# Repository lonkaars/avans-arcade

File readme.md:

# Hooded Havoc: Miniboss Mania

(working title)

## hardware

- stm32 (f091rc)
- basys3 (xc7a35tcpg236-1)

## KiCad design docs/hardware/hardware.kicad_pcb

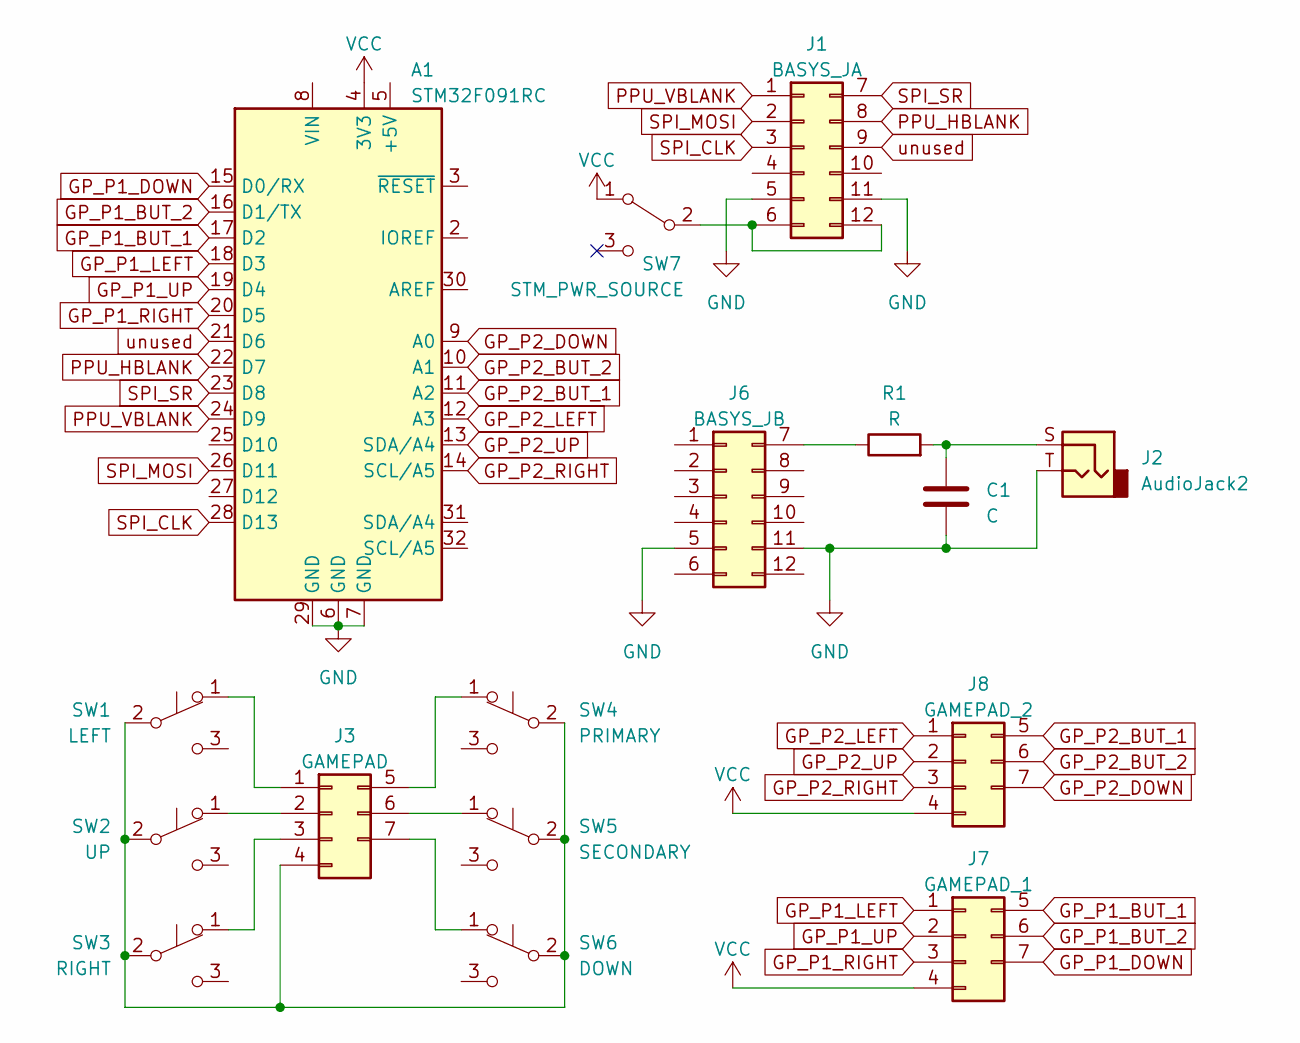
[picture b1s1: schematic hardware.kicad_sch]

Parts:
A1: STM32F091RC; Arduino_UNO_R3
C1: C; C_Disc_D6.0mm_W2.5mm_P5.00mm
J1: BASYS_JA; PinHeader_2x06_P2.54mm_Vertical
J2: AudioJack2; Jack_3.5mm_CUI_SJ1-3523N_Horizontal
J3: GAMEPAD; PinHeader_2x04_P2.54mm_Vertical
J6: BASYS_JB; PinHeader_2x06_P2.54mm_Vertical
J7: GAMEPAD_1; PinHeader_2x04_P2.54mm_Vertical
J8: GAMEPAD_2; PinHeader_2x04_P2.54mm_Vertical
R1: R; R_Axial_DIN0207_L6.3mm_D2.5mm_P7.62mm_Horizontal
SW1: LEFT; SW_PUSH_6mm
SW2: UP; SW_PUSH_6mm
SW3: RIGHT; SW_PUSH_6mm
SW4: PRIMARY; SW_PUSH_6mm
SW5: SECONDARY; SW_PUSH_6mm
SW6: DOWN; SW_PUSH_6mm
SW7: STM_PWR_SOURCE; SW_Slide_1P2T_CK_OS102011MS2Q

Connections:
GND: A1.6 (GND), A1.7 (GND), A1.29 (GND), C1.2, J1.5, J1.11, J2.T, J6.5, J6.11
GP_P1_BUT_1: A1.17 (D2), J7.5 (RIGHT)
GP_P1_BUT_2: A1.16 (D1/TX), J7.6 (PRIMARY)
GP_P1_DOWN: A1.15 (D0/RX), J7.7 (SECONDARY)
GP_P1_LEFT: A1.18 (D3), J7.1 (UP)
GP_P1_RIGHT: A1.20 (D5), J7.3 (LEFT)
GP_P1_UP: A1.19 (D4), J7.2 (DOWN)
GP_P2_BUT_1: A1.11 (A2), J8.5 (RIGHT)
GP_P2_BUT_2: A1.10 (A1), J8.6 (PRIMARY)
GP_P2_DOWN: A1.9 (A0), J8.7 (SECONDARY)
GP_P2_LEFT: A1.12 (A3), J8.1 (UP)
GP_P2_RIGHT: A1.14 (SCL/A5), J8.3 (LEFT)
GP_P2_UP: A1.13 (SDA/A4), J8.2 (DOWN)
unnamed: C1.1, J2.S, R1.2
unnamed: J1.6, J1.12, SW7.2 (B)
unnamed: J3.2 (DOWN), SW2.1 (A)
unnamed: J3.3 (LEFT), SW3.1 (A)
unnamed: J3.6 (PRIMARY), SW5.1 (A)
unnamed: J3.5 (RIGHT), SW4.1 (A)
unnamed: J3.7 (SECONDARY), SW6.1 (A)
unnamed: J3.1 (UP), SW1.1 (A)
unnamed: J3.4 (VCC), SW1.2 (B), SW2.2 (B), SW3.2 (B), SW4.2 (B), SW5.2 (B), SW6.2 (B)
unnamed: J6.7, R1.1
PPU_HBLANK: A1.22 (D7), J1.8
PPU_VBLANK: A1.24 (D9), J1.1
SPI_CLK: A1.28 (D13), J1.3
SPI_MOSI: A1.26 (D11), J1.2
SPI_SR: A1.23 (D8), J1.7
VCC: A1.4 (3V3), J7.4 (VCC), J8.4 (VCC), SW7.1 (A)
unused: A1.21 (D6), J1.9

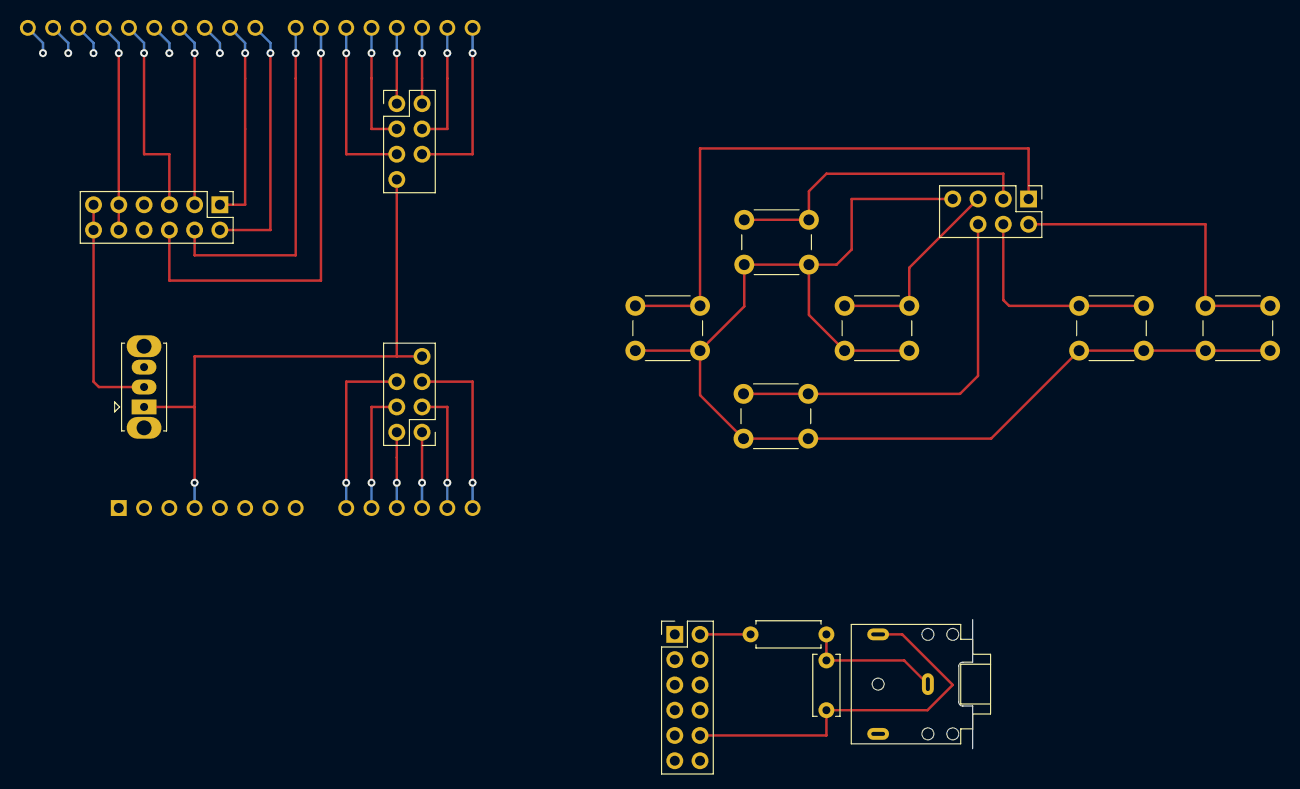
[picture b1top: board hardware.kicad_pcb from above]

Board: 2 copper layers, 16 parts (1 on the bottom side), 30 nets.

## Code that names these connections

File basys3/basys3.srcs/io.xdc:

set_property IOSTANDARD LVCMOS33 [get_ports SPI_MOSI]
set_property PACKAGE_PIN L2 [get_ports SPI_MOSI]

set_property PACKAGE_PIN J2 [get_ports SPI_CLK]
set_property IOSTANDARD LVCMOS33 [get_ports SPI_CLK]

set_property IOSTANDARD LVCMOS33 [get_ports SPI_SR]
set_property PACKAGE_PIN H1 [get_ports SPI_SR]
set_property PULLDOWN true [get_ports SPI_SR]



set_property IOSTANDARD LVCMOS33 [get_ports HBLANK]
set_property PACKAGE_PIN K2 [get_ports HBLANK]

set_property IOSTANDARD LVCMOS33 [get_ports VBLANK]
set_property PACKAGE_PIN J1 [get_ports VBLANK]



set_property IOSTANDARD LVCMOS33 [get_ports SYSCLK]
set_property PACKAGE_PIN W5 [get_ports SYSCLK]

set_property IOSTANDARD LVCMOS33 [get_ports RESET]
set_property PACKAGE_PIN T18 [get_ports RESET]

set_property IOSTANDARD LVCMOS33 [get_ports HSYNC]
set_property IOSTANDARD LVCMOS33 [get_ports VSYNC]

set_property PACKAGE_PIN P19 [get_ports HSYNC]
set_property PACKAGE_PIN R19 [get_ports VSYNC]

set_property IOSTANDARD LVCMOS33 [get_ports {R[3]}]
set_property IOSTANDARD LVCMOS33 [get_ports {R[2]}]
set_property IOSTANDARD LVCMOS33 [get_ports {R[1]}]
set_property IOSTANDARD LVCMOS33 [get_ports {R[0]}]
set_property IOSTANDARD LVCMOS33 [get_ports {G[3]}]
set_property IOSTANDARD LVCMOS33 [get_ports {G[2]}]
set_property IOSTANDARD LVCMOS33 [get_ports {G[1]}]
set_property IOSTANDARD LVCMOS33 [get_ports {G[0]}]
set_property IOSTANDARD LVCMOS33 [get_ports {B[3]}]
set_property IOSTANDARD LVCMOS33 [get_ports {B[2]}]
set_property IOSTANDARD LVCMOS33 [get_ports {B[1]}]
set_property IOSTANDARD LVCMOS33 [get_ports {B[0]}]

set_property PACKAGE_PIN N19 [get_ports {R[3]}]
set_property PACKAGE_PIN J19 [get_ports {R[2]}]
set_property PACKAGE_PIN H19 [get_ports {R[1]}]
set_property PACKAGE_PIN G19 [get_ports {R[0]}]
set_property PACKAGE_PIN D17 [get_ports {G[3]}]
set_property PACKAGE_PIN G17 [get_ports {G[2]}]
set_property PACKAGE_PIN H17 [get_ports {G[1]}]
set_property PACKAGE_PIN J17 [get_ports {G[0]}]
set_property PACKAGE_PIN J18 [get_ports {B[3]}]
set_property PACKAGE_PIN K18 [get_ports {B[2]}]
set_property PACKAGE_PIN L18 [get_ports {B[1]}]
set_property PACKAGE_PIN N18 [get_ports {B[0]}]

set_property IOSTANDARD LVCMOS33 [get_ports DBG_DISP_ADDR]
set_property PACKAGE_PIN R2 [get_ports DBG_DISP_ADDR]
set_property IOSTANDARD LVCMOS33 [get_ports {DBG_LEDS_OUT[15]}]
set_property IOSTANDARD LVCMOS33 [get_ports {DBG_LEDS_OUT[14]}]
set_property IOSTANDARD LVCMOS33 [get_ports {DBG_LEDS_OUT[13]}]
set_property IOSTANDARD LVCMOS33 [get_ports {DBG_LEDS_OUT[12]}]
set_property IOSTANDARD LVCMOS33 [get_ports {DBG_LEDS_OUT[11]}]
set_property IOSTANDARD LVCMOS33 [get_ports {DBG_LEDS_OUT[10]}]
set_property IOSTANDARD LVCMOS33 [get_ports {DBG_LEDS_OUT[8]}]
set_property IOSTANDARD LVCMOS33 [get_ports {DBG_LEDS_OUT[9]}]
set_property IOSTANDARD LVCMOS33 [get_ports {DBG_LEDS_OUT[7]}]
set_property IOSTANDARD LVCMOS33 [get_ports {DBG_LEDS_OUT[6]}]
set_property IOSTANDARD LVCMOS33 [get_ports {DBG_LEDS_OUT[5]}]
set_property IOSTANDARD LVCMOS33 [get_ports {DBG_LEDS_OUT[4]}]
set_property IOSTANDARD LVCMOS33 [get_ports {DBG_LEDS_OUT[3]}]
set_property IOSTANDARD LVCMOS33 [get_ports {DBG_LEDS_OUT[2]}]
set_property IOSTANDARD LVCMOS33 [get_ports {DBG_LEDS_OUT[1]}]
set_property IOSTANDARD LVCMOS33 [get_ports {DBG_LEDS_OUT[0]}]
set_property PACKAGE_PIN L1 [get_ports {DBG_LEDS_OUT[15]}]
set_property PACKAGE_PIN P1 [get_ports {DBG_LEDS_OUT[14]}]
set_property PACKAGE_PIN N3 [get_ports {DBG_LEDS_OUT[13]}]
set_property PACKAGE_PIN P3 [get_ports {DBG_LEDS_OUT[12]}]
set_property PACKAGE_PIN U3 [get_ports {DBG_LEDS_OUT[11]}]
set_property PACKAGE_PIN W3 [get_ports {DBG_LEDS_OUT[10]}]
set_property PACKAGE_PIN V3 [get_ports {DBG_LEDS_OUT[9]}]
set_property PACKAGE_PIN V13 [get_ports {DBG_LEDS_OUT[8]}]
set_property PACKAGE_PIN V14 [get_ports {DBG_LEDS_OUT[7]}]
set_property PACKAGE_PIN U14 [get_ports {DBG_LEDS_OUT[6]}]
set_property PACKAGE_PIN U15 [get_ports {DBG_LEDS_OUT[5]}]
set_property PACKAGE_PIN W18 [get_ports {DBG_LEDS_OUT[4]}]
set_property PACKAGE_PIN V19 [get_ports {DBG_LEDS_OUT[3]}]
set_property PACKAGE_PIN U19 [get_ports {DBG_LEDS_OUT[2]}]
set_property PACKAGE_PIN E19 [get_ports {DBG_LEDS_OUT[1]}]
set_property PACKAGE_PIN U16 [get_ports {DBG_LEDS_OUT[0]}]


set_property CONFIG_VOLTAGE 3.3 [current_design]
set_property CFGBVS VCCO [current_design]

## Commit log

2023-02-02 added sound chips research
2023-02-03 rename sound chip research to research.md
2023-02-03 beginning of gpu research added
2023-02-03 add makefile for bin tests
2023-02-05 add more PPU design
2023-02-06 add spreadsheet link to research.md
2023-02-07 more PPU documentation
2023-02-08 more PPU design
2023-02-08 more PPU (level 3 design)
2023-02-09 add style guide + formatters
2023-02-10 PPU resolution change
2023-02-11 added gameplay concept
2023-02-12 Create Research game engine
2023-02-13 Research - FPGA audio generation
2023-02-13 player sprite concept
2023-02-13 Create Game Idea Bjorn
2023-02-13 Mijn toevegingen
2023-02-13 test
2023-02-13 Added Bjorn concept
2023-02-13 elaborate gameplay concept
2023-02-14 add student ids to document template
2023-02-14 fix line wrapping in gameplay.md
2023-02-14 move architecture from research into architecture.md and update ppu design files
2023-02-14 architecture top-level added
2023-02-15 GameEngine
2023-02-15 Quick spelling check
2023-02-15 APU Archetecture.md
2023-02-15 Update architecture.md
    Updated controller design
2023-02-15 fix markdown for document converter
2023-02-15 architecture
2023-02-15 APU tone generation
2023-02-15 final architecture document version
2023-02-17 fix project name in document template
2023-02-17 WIP ppu.vhdl
2023-02-17 safety commit (before remove DI lines)
2023-02-17 separate AUX memory into separate component
2023-02-17 use tabs for indentation
2023-02-18 ppu pceg done + ppu top.vhdl done
2023-02-18 no clock output while reset high in pceg
2023-02-19 apu note 2 freq
2023-02-19 single frequency implementation
2023-02-19 apu_LUT_reader made with variable frequency
2023-02-19 add list of abbreviations to docs folder
2023-02-19 separate constants file for vhdl code
2023-02-19 finish ppu address decoder
2023-02-19 format and add apu sources to vivado project file
2023-02-19 polish on APU_N2F
2023-02-19 hello world over usb serial done
2023-02-19 shifted triangle wave 180*
2023-02-19 small formatting fix
2023-02-19 POC done
2023-02-20 rename .vhdl to .vhd
2023-02-20 exposed ram module implemented
2023-02-20 update code style
2023-02-20 PPU AUX memory finished and tested
2023-02-20 update TMM data width + update memory map (WIP ppu_sprite_bg)
2023-02-20 PPU background sprite component done (but unverified)
2023-02-21 fix sprite flip axes swapped
2023-02-21 PPU debugged and working (but with unwanted latches)
2023-02-21 background sprite component done, tested, and working without latches
2023-02-21 WIP ppu foreground sprite component
2023-02-21 WIP foreground sprite + `std_logic_vector` -> `unsigned` mess
2023-02-22 WIP ppu fg sprite fetch logic
2023-02-23 ppu foreground sprite working and ~50% tested
2023-02-23 plut,comp en vga
2023-02-23 sdl2 demo
2023-02-23 clock
    interne clcok toegevoegd aan de vga modules. niks is veranderd aan de PLUT want die werkt nog steeds op dezelfde SYSCLK.
2023-02-23 aanpassingen
    was counter naar 0 vergeten
2023-02-24 WIP ppu interface
2023-02-24 update style guide and format code
2023-02-24 rename and move files
2023-02-24 desktop compilation options in makefile
2023-02-24 mv sdl2 demo to src/ppusim folder
2023-02-24 ppusim refactor
2023-02-24 c interface semi-done
2023-02-24 WIP ppusim
2023-02-24 background sprites working in ppusim
2023-02-25 ppusim done
2023-02-25 optimize ppusim with threads
2023-02-25 update/fix build config for windows
2023-02-25 limit thread count to core count
2023-02-25 add developer documentation to ppusim/ppu interface
2023-02-25 fix src readme
2023-02-25 fix compiler warnings from `hh_ppu_vram_valid_address`
2023-03-01 WIP addr_dec timing check + ppu address bus fix
2023-03-02 ExampleCode For physics
2023-03-03 apu constants cleanup
2023-03-03 file cleanup
2023-03-03 fix apu_note_to_frequency
2023-03-03 WIP fg sprite optimilization
2023-03-03 State digrams for gameLogic
2023-03-03 fix naming style
2023-03-03 New Folder for stm32 gamelogic
2023-03-03 Player movement x/y with collision map
    Player can move in x and y direction via 4 buttons
    Furthermore there is a tilemap included for collisions for coresponding map design
2023-03-03 changed to .md and added pin layout
2023-03-03 Changed to tables
2023-03-03 Cleaned main.c
2023-03-04 foreground sprite optimization (untested) done
2023-03-04 fix multiple driver net errors
2023-03-07 some func defenitions for game-engine and foundation
2023-03-08 more todo's
2023-03-08 fix windows build system and add vscode configuration files
2023-03-08 scaffold vga display controller and upscaler
2023-03-08 spelling correction
2023-03-08 WIP dispctl
2023-03-08 more WIP dispctl
2023-03-08 ppu dispctl WIP (shift XY output 2 scanlines and send THVBLANK)
2023-03-08 ppu_dispctl test for valid VGA signal using DMT 640x480 @ 60
2023-03-09 Add files via upload
    Updated with functions
2023-03-10 code
2023-03-10 added define for fixed point maths
2023-03-10 nope
2023-03-10 initial merge of #26
2023-03-10 add input emulation to test collision
2023-03-10 `clang-format`
2023-03-10 update style guide
2023-03-10 fixed code styles
2023-03-10 move pinout.md to schematic
2023-03-10 top.vhdl
2023-03-10 ppusim read sprites from file and put into vram
2023-03-10 removed TODO
2023-03-11 moved files
2023-03-11 Camera function V1
2023-03-11 makefile engine
2023-03-11 Camera.c and Camera.h
2023-03-11 add display diagram for ppu
2023-03-11 drawing map en read from binary complete. shift to background.
2023-03-11 Fixed movement
    Adjusted movement speed otherwise wouldnt show any movement. Also changed input testing lines so it does work
2023-03-12 integrated palettes and fixed reading tiles
2023-03-12 syntax update
2023-03-12 camera movement
2023-03-12 makefile update
2023-03-12 WIP dispctl (valid VGA signal)
2023-03-12 upscaler test with coe initialized rom
2023-03-13 features voor ons spel
2023-03-13 camera, movement, collisions
2023-03-13 demo.c
2023-03-13 camera.c en camera.h
2023-03-13 Background collision
    Added background collision for player and other entities. Added gravity and jump functionailty
2023-03-13 demo.c clean up
2023-03-13 Revert "Merge branch 'dev' of https://github.com/Flenk008/avans-arcade into dev"
    This reverts commit 4f489426e05fb3b296998b17859d8702cc4f37e1, reversing
    changes made to e47f7fa198229b8598b8ab03ef8b2483f7c685bc.
2023-03-13 Revert "Background collision"
    This reverts commit e47f7fa198229b8598b8ab03ef8b2483f7c685bc.
2023-03-13 Revert "Revert "Merge branch 'dev' of https://github.com/Flenk008/avans-arcade into dev""
    This reverts commit a9ad8e0a8ac5346108f1e2c1a0bf9360fadc20da.
2023-03-13 fix display upscaler (output working!)
2023-03-13 working bitstream generation
2023-03-13 untested POC
2023-03-13 fix write enable input line
2023-03-14 camera y-axis bug fixed + clean up
2023-03-14 update hardware schematics for ppu testing
2023-03-14 added hexdump file structures
2023-03-14 WIP ppu testing
2023-03-14 finalize hardware
2023-03-14 add fp-info-cache to gitignore
2023-03-15 precautions
2023-03-15 game loop and bullet
    TODO game loop:
    -(startingscreen) read correct indexes
    -(shop) read correct indexes
    -gameplay still needs alot with different levels etc..
    rest not yet done
    bullet needs testing and correct PAL and tilemap reading
2023-03-15 architecture docu
2023-03-15 Player-Enemy collision
    Added player with enemy collision. Also changed input system to a vector system with friction and gravity. Jump also works. Enemy is 1 stationary object.
2023-03-15 architecture and design
2023-03-15 added title screen
2023-03-15 Update features.md
    Added Dubble Jump
2023-03-15 updated file fetch
2023-03-15 (UNCLEAN) partial merge of #37
2023-03-15 architecture document update
2023-03-16 Added top level stm
2023-03-16 Update architecture.md
    Added SPI (STM32, BASYS3)
2023-03-16 restructure architecture document
2023-03-20 debugged the ppu (still WIP, but some output is visible)
2023-03-20 faster SPI clock
2023-03-20 demo version
2023-03-22 merge
2023-03-22 tilemap build system done
2023-03-22 add static makefile targets to main gamefile, and add target to flash static rom to stm32
2023-03-22 fix endianness in `tilepack` and add `tilemap2png` script for previewing finished tilemap
2023-03-22 Animated jumpable slime
2023-03-22 updated test/bin/.gitignore
2023-03-22 added normal slime animations
2023-03-22 load static/tilemap.bin in ppusim
2023-03-23 use sort order in makefile and add air tile at index 0
2023-03-23 added font.hex
2023-03-23 fixed slime.hex
2023-03-23 add scripts for converting tiles to separate png images for tilemap editing
2023-03-23 WIP testing ppu (fixed BAM 2nat buffer overflow)
2023-03-24 add power source toggle switch to hardware schematics
2023-03-24 added first pass on animation systems
2023-03-24 a little clean up of player_controller.c
2023-03-29 update pipeline
2023-03-29 more debugging WIP
2023-03-30 gameloop/bullet/levels
    gameloop moet nog wat gefixt worden. shop moet nog wat art en functie krijgen zefde voor gameover/highscore
    bullet moet meerdere entityten kunnen doen nu nog alleen gemaakt voor 1.
    levels moet alleen nog backwords kunnen
2023-03-30 new spi system
2023-03-30 spi not working on hardware
2023-03-31 it's working
2023-04-02 snake case/background
2023-04-03 misc/cleanup
2023-04-03 shop statemachine
2023-04-03 sprite rendering, collision fix
2023-04-03 shop selections done
2023-04-03 hh_update_sprite is now a void function
2023-04-03 player controller update
2023-04-03 worky but janky integration done
2023-04-03 connect remaining ppu lines to stm
2023-04-03 update i/o in vhdl and minor improvements
2023-04-03 removed nrf from settings.json
2023-04-03 multiple bullets and bg collisions.
2023-04-04 Enemy AI
2023-04-04 final I/O edits
2023-04-04 dynamic tilemap integration (without pallets)
2023-04-04 bullet/player/enemy/gameplay
    bullet only needs different directions
    player is done
    enemy needs ai(Bjorn)
    gameplay may need some finetuning
2023-04-04 full ppu IO in stm code (h/vblank interrupts)
2023-04-04 remove pull down resistor for SPI SR and test new SPI transmit
2023-04-04 minor pcb cleanup
2023-04-04 WIP DMA SPI TX
2023-04-05 Dynamic tilemap works
2023-04-05 enemy and ai, bullets and gameplay
    ai needs finetuning
2023-04-06 rendering hp + strings
2023-04-06 dma send done and working
2023-04-06 printing strings coming to YOUR screen!
2023-04-06 random shop items + animations
2023-04-07 added highscore screen with kb nav
2023-04-07 WIP more debugging
2023-04-07 last-ditch debugging efforts
2023-04-15 fix demo figure
2023-04-16 more debugging
2023-04-16 don't point openfpgaloader to home directory
2023-05-29 remove unneeded dependency on test
2023-05-29 add controller test and swap p1 and p2
2023-05-31 Working start integration
2023-05-31 add static map
2023-05-31 scripts
2023-05-31 WIP porting
2023-06-04 grammar + fact check + add todo's
2023-06-09 introduction changed
